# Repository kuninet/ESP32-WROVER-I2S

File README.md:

# ESP32-WROVER + I2S DACを使ったAirPlay、Bluetooth再生基板

## 概要

* ESP32-WROVER + I2S DACを使ったAirPlay、Bluetooth再生基板です。
* ファームウェアは、[squeezelite-esp32](https://github.com/sle118/squeezelite-esp32)を使用させていただきます。
  * https://github.com/sle118/squeezelite-esp32
* ファームウェアの書き込みには、ESP32 Downloader kitや、拙作[ESP32-Downloader](https://github.com/kuninet/ESP32-Downloader)をご使用ください。

## ☆現在 プリント基板を試作して確認中です。★

## 参考
* [ESP32でBluetooth／AirPlayスピーカーを作る](https://note.com/6ihwd/n/ncfccd1f401a1)
* [squeezelite-esp32](https://github.com/sle118/squeezelite-esp32)
* [zynthian-miniature](https://github.com/sstojos/zynthian-miniature)
* [KiCad Footprint and Component for ESP32-Wrover](https://github.com/aliafshar/esp32-wrover-kicad)

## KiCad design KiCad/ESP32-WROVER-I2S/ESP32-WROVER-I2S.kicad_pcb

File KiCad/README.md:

# ESP32-WROVER + I2S DACを使ったAirPlay、Bluetooth再生基板

## 概要

* ESP32-WROVER + I2S DACを使ったAirPlay、Bluetooth再生基板です。
* ファームウェアは、[squeezelite-esp32](https://github.com/sle118/squeezelite-esp32)を使用させていただきます。
  * https://github.com/sle118/squeezelite-esp32

## 参考
* [ESP32でBluetooth／AirPlayスピーカーを作る](https://note.com/6ihwd/n/ncfccd1f401a1)
* [squeezelite-esp32](https://github.com/sle118/squeezelite-esp32
* [zynthian-miniature](https://github.com/sstojos/zynthian-miniature)
* [KiCad Footprint and Component for ESP32-Wrover](https://github.com/aliafshar/esp32-wrover-kicad)

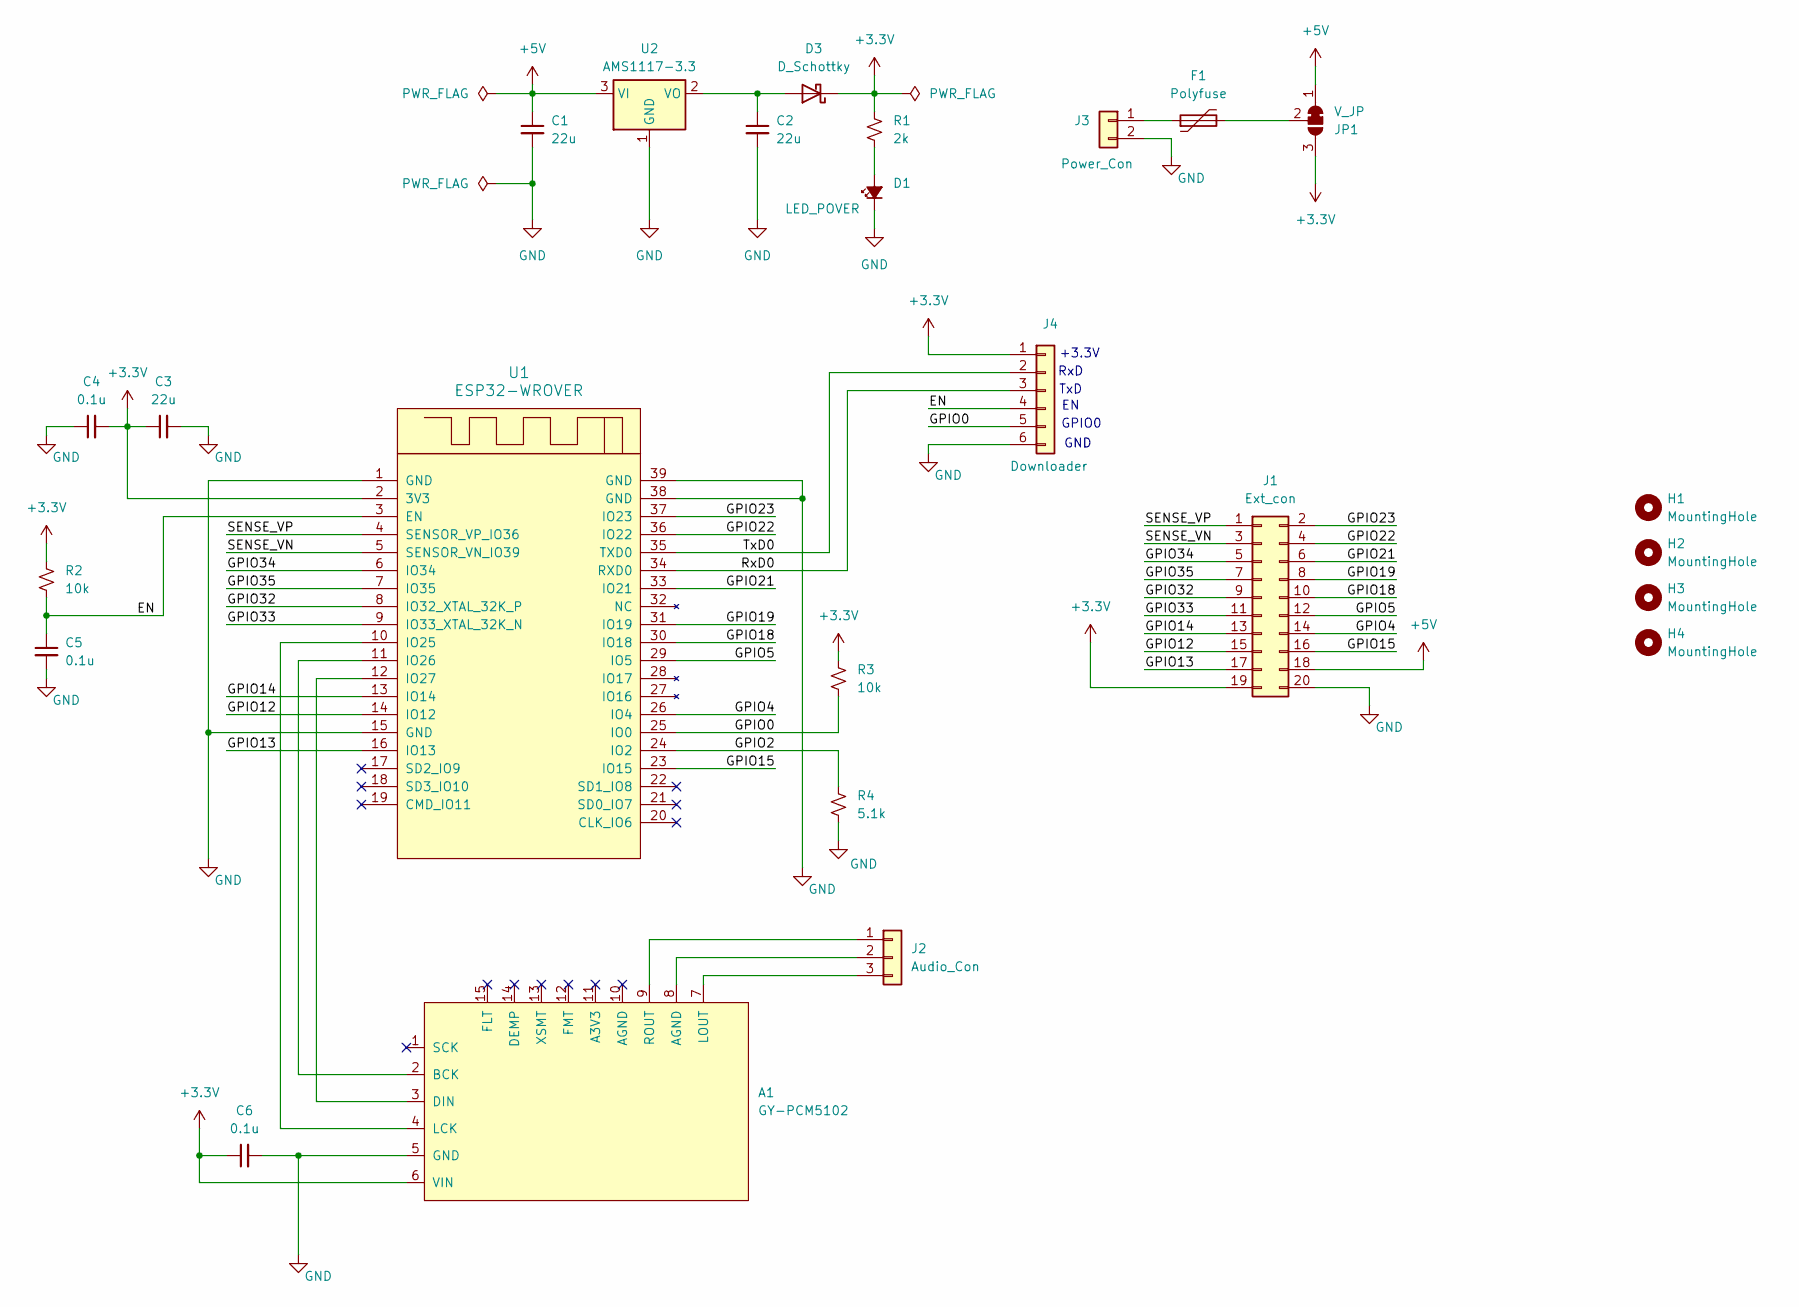
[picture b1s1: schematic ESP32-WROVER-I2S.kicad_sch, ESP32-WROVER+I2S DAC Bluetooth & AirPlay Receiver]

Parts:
A1: GY-PCM5102
C1, C2, C3: 22u; C_0603_1608Metric_Pad1.08x0.95mm_HandSolder
C4, C5, C6: 0.1u; C_0603_1608Metric_Pad1.08x0.95mm_HandSolder
D1: LED_POVER; LED_0603_1608Metric_Pad1.05x0.95mm_HandSolder
D3: D_Schottky; D_SOD-123
F1: Polyfuse; Fuse_1206_3216Metric_Pad1.42x1.75mm_HandSolder
H1, H2, H3, H4: MountingHole; MountingHole_3.2mm_M3
J1: Ext_con; PinHeader_2x10_P2.54mm_Vertical
J2: Audio_Con; JST_XH_B3B-XH-A_1x03_P2.50mm_Vertical
J3: Power_Con; JST_XH_B2B-XH-A_1x02_P2.50mm_Vertical
J4: Downloader; PinSocket_1x06_P2.54mm_Vertical
JP1: V_JP; SolderJumper-3_P1.3mm_Bridged12_Pad1.0x1.5mm_NumberLabels
R1: 2k; R_0603_1608Metric_Pad0.98x0.95mm_HandSolder
R2, R3: 10k; R_0603_1608Metric_Pad0.98x0.95mm_HandSolder
R4: 5.1k; R_0603_1608Metric_Pad0.98x0.95mm_HandSolder
U1: ESP32-WROVER
U2: AMS1117-3.3; SOT-223-3_TabPin2

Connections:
+3.3V: A1.6 (VIN), C3.1, C4.2, C6.1, D3.1 (K), J1.19, J4.1, JP1.3 (B), R1.1, R2.1, R3.1, U1.2 (3V3)
+5V: C1.1, J1.18, JP1.1 (A), U2.3 (VI)
/EN: C5.1, J4.4, R2.2, U1.3 (EN)
/GPIO0: J4.5, R3.2, U1.25 (IO0)
/GPIO2: R4.1, U1.24 (IO2)
/GPIO4: J1.14, U1.26 (IO4)
/GPIO5: J1.12, U1.29 (IO5)
/GPIO12: J1.15, U1.14 (IO12)
/GPIO13: J1.17, U1.16 (IO13)
/GPIO14: J1.13, U1.13 (IO14)
/GPIO15: J1.16, U1.23 (IO15)
/GPIO18: J1.10, U1.30 (IO18)
/GPIO19: J1.8, U1.31 (IO19)
/GPIO21: J1.6, U1.33 (IO21)
/GPIO22: J1.4, U1.36 (IO22)
/GPIO23: J1.2, U1.37 (IO23)
/GPIO32: J1.9, U1.8 (IO32_XTAL_32K_P)
/GPIO33: J1.11, U1.9 (IO33_XTAL_32K_N)
/GPIO34: J1.5, U1.6 (IO34)
/GPIO35: J1.7, U1.7 (IO35)
/RxD0: J4.3, U1.34 (RXD0)
/SENSE_VN: J1.3, U1.5 (SENSOR_VN_IO39)
/SENSE_VP: J1.1, U1.4 (SENSOR_VP_IO36)
/TxD0: J4.2, U1.35 (TXD0)
GND: A1.5 (GND), C1.2, C2.2, C3.2, C4.1, C5.2, C6.2, D1.1 (K), J1.20, J3.2, J4.6, R4.2, U1.1 (GND), U1.15 (GND), U1.38 (GND), U1.39 (GND), U2.1 (GND)
unnamed: A1.2 (BCK), U1.11 (IO26)
unnamed: A1.3 (DIN), U1.12 (IO27)
unnamed: A1.4 (LCK), U1.10 (IO25)
unnamed: A1.7 (LOUT), J2.3
unnamed: A1.9 (ROUT), J2.1
unnamed: D1.2 (A), R1.2
unnamed: C2.1, D3.2 (A), U2.2 (VO)
unnamed: A1.8 (AGND), J2.2
unnamed: F1.1, J3.1
unnamed: F1.2, JP1.2 (C)

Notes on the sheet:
GND
+3.3V
RxD
GPIO0
TxD

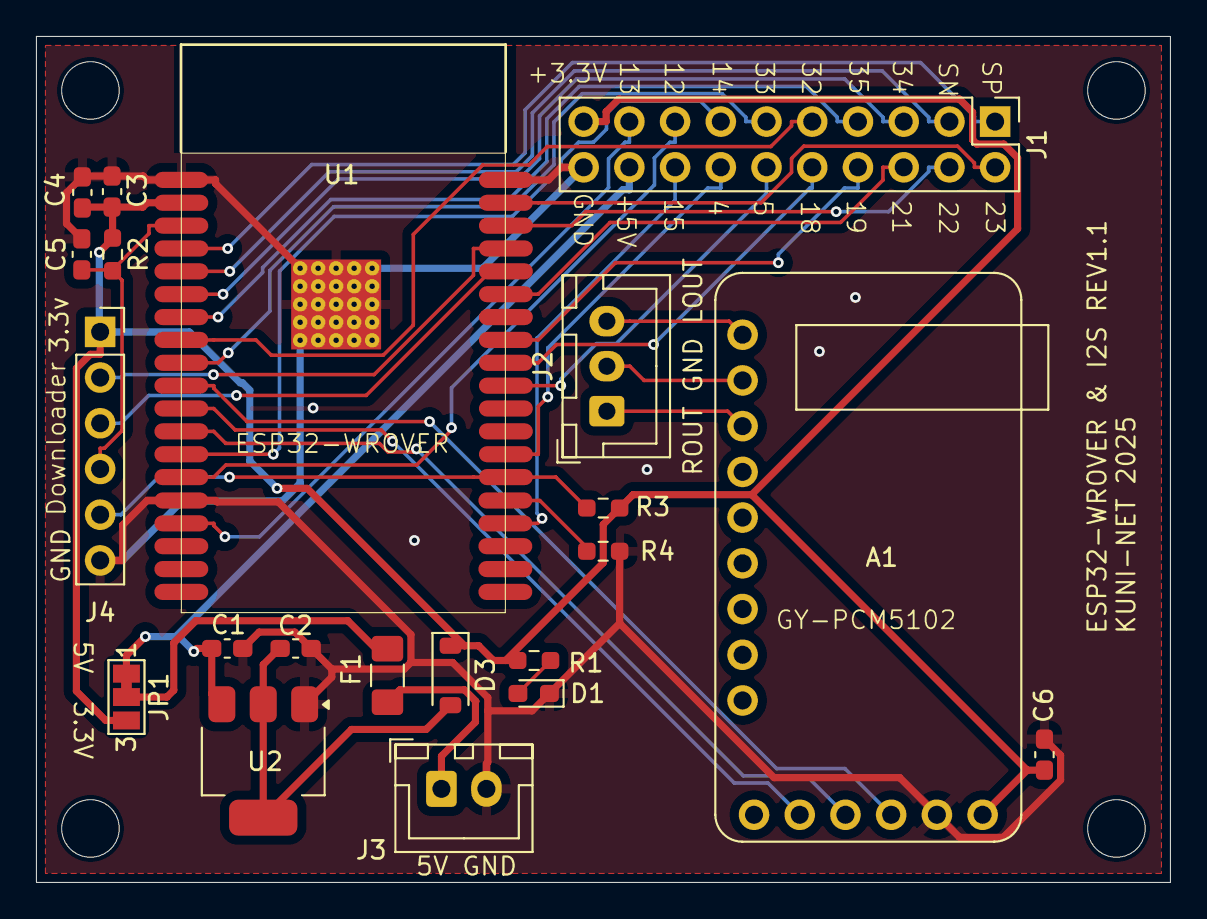
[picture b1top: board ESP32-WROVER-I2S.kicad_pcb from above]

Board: 2 copper layers, 63.0 x 47.0 mm, 25 parts (0 on the bottom side), 35 nets.

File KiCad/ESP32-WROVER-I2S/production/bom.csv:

Designator,Footprint,Quantity,Value,LCSC Part #
A1,GY-PCM5102,1,GY-PCM5102,
"C1, C2, C3",0603,3,22u,
"C4, C5, C6",0603,3,0.1u,
D1,0603,1,LED_POVER,
D3,D_SOD-123,1,D_Schottky,
F1,1206,1,Polyfuse,
J1,PinHeader_2x10_P2.54mm_Vertical,1,Ext_con,
J2,JST_XH_B3B-XH-A_1x03_P2.50mm_Vertical,1,Audio_Con,
J3,JST_XH_B2B-XH-A_1x02_P2.50mm_Vertical,1,Power_Con,
J4,PinSocket_1x06_P2.54mm_Vertical,1,Downloader,
R1,0603,1,2k,
"R2, R3",0603,2,10k,
R4,0603,1,5.1k,
U1,ESP32-WROVER,1,ESP32-WROVER,
U2,SOT-223-3_TabPin2,1,AMS1117-3.3,

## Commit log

2025-05-18 init commit
2025-05-18 README移動
2025-05-18 Create LICENSE
2025-05-18 基板イメージ添付
2025-06-28 ガーバー出力
2025-06-29 5v/3.3v切り替えジャンパ追加、電源LED変更、REV1.1ガーバー出力
